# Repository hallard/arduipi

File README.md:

ArduiPi
=======

ArduiPi is a shield for Raspberry Pi that brings Arduino low level extented I/O to Raspberry Pi.

Detailed Description
====================

Everything is documented on this decicated [page][3]

**Schematic**  

**Board**  
![board] (https://raw.github.com/hallard/arduipi/master/ArduiPi-V1.1-brd.png)

Check out news and other projects on my [blog][4] 

[3]: http://hallard.me/arduipi-the-shield-that-brings-arduino-to-raspberry-pi/
[4]: http://hallard.me

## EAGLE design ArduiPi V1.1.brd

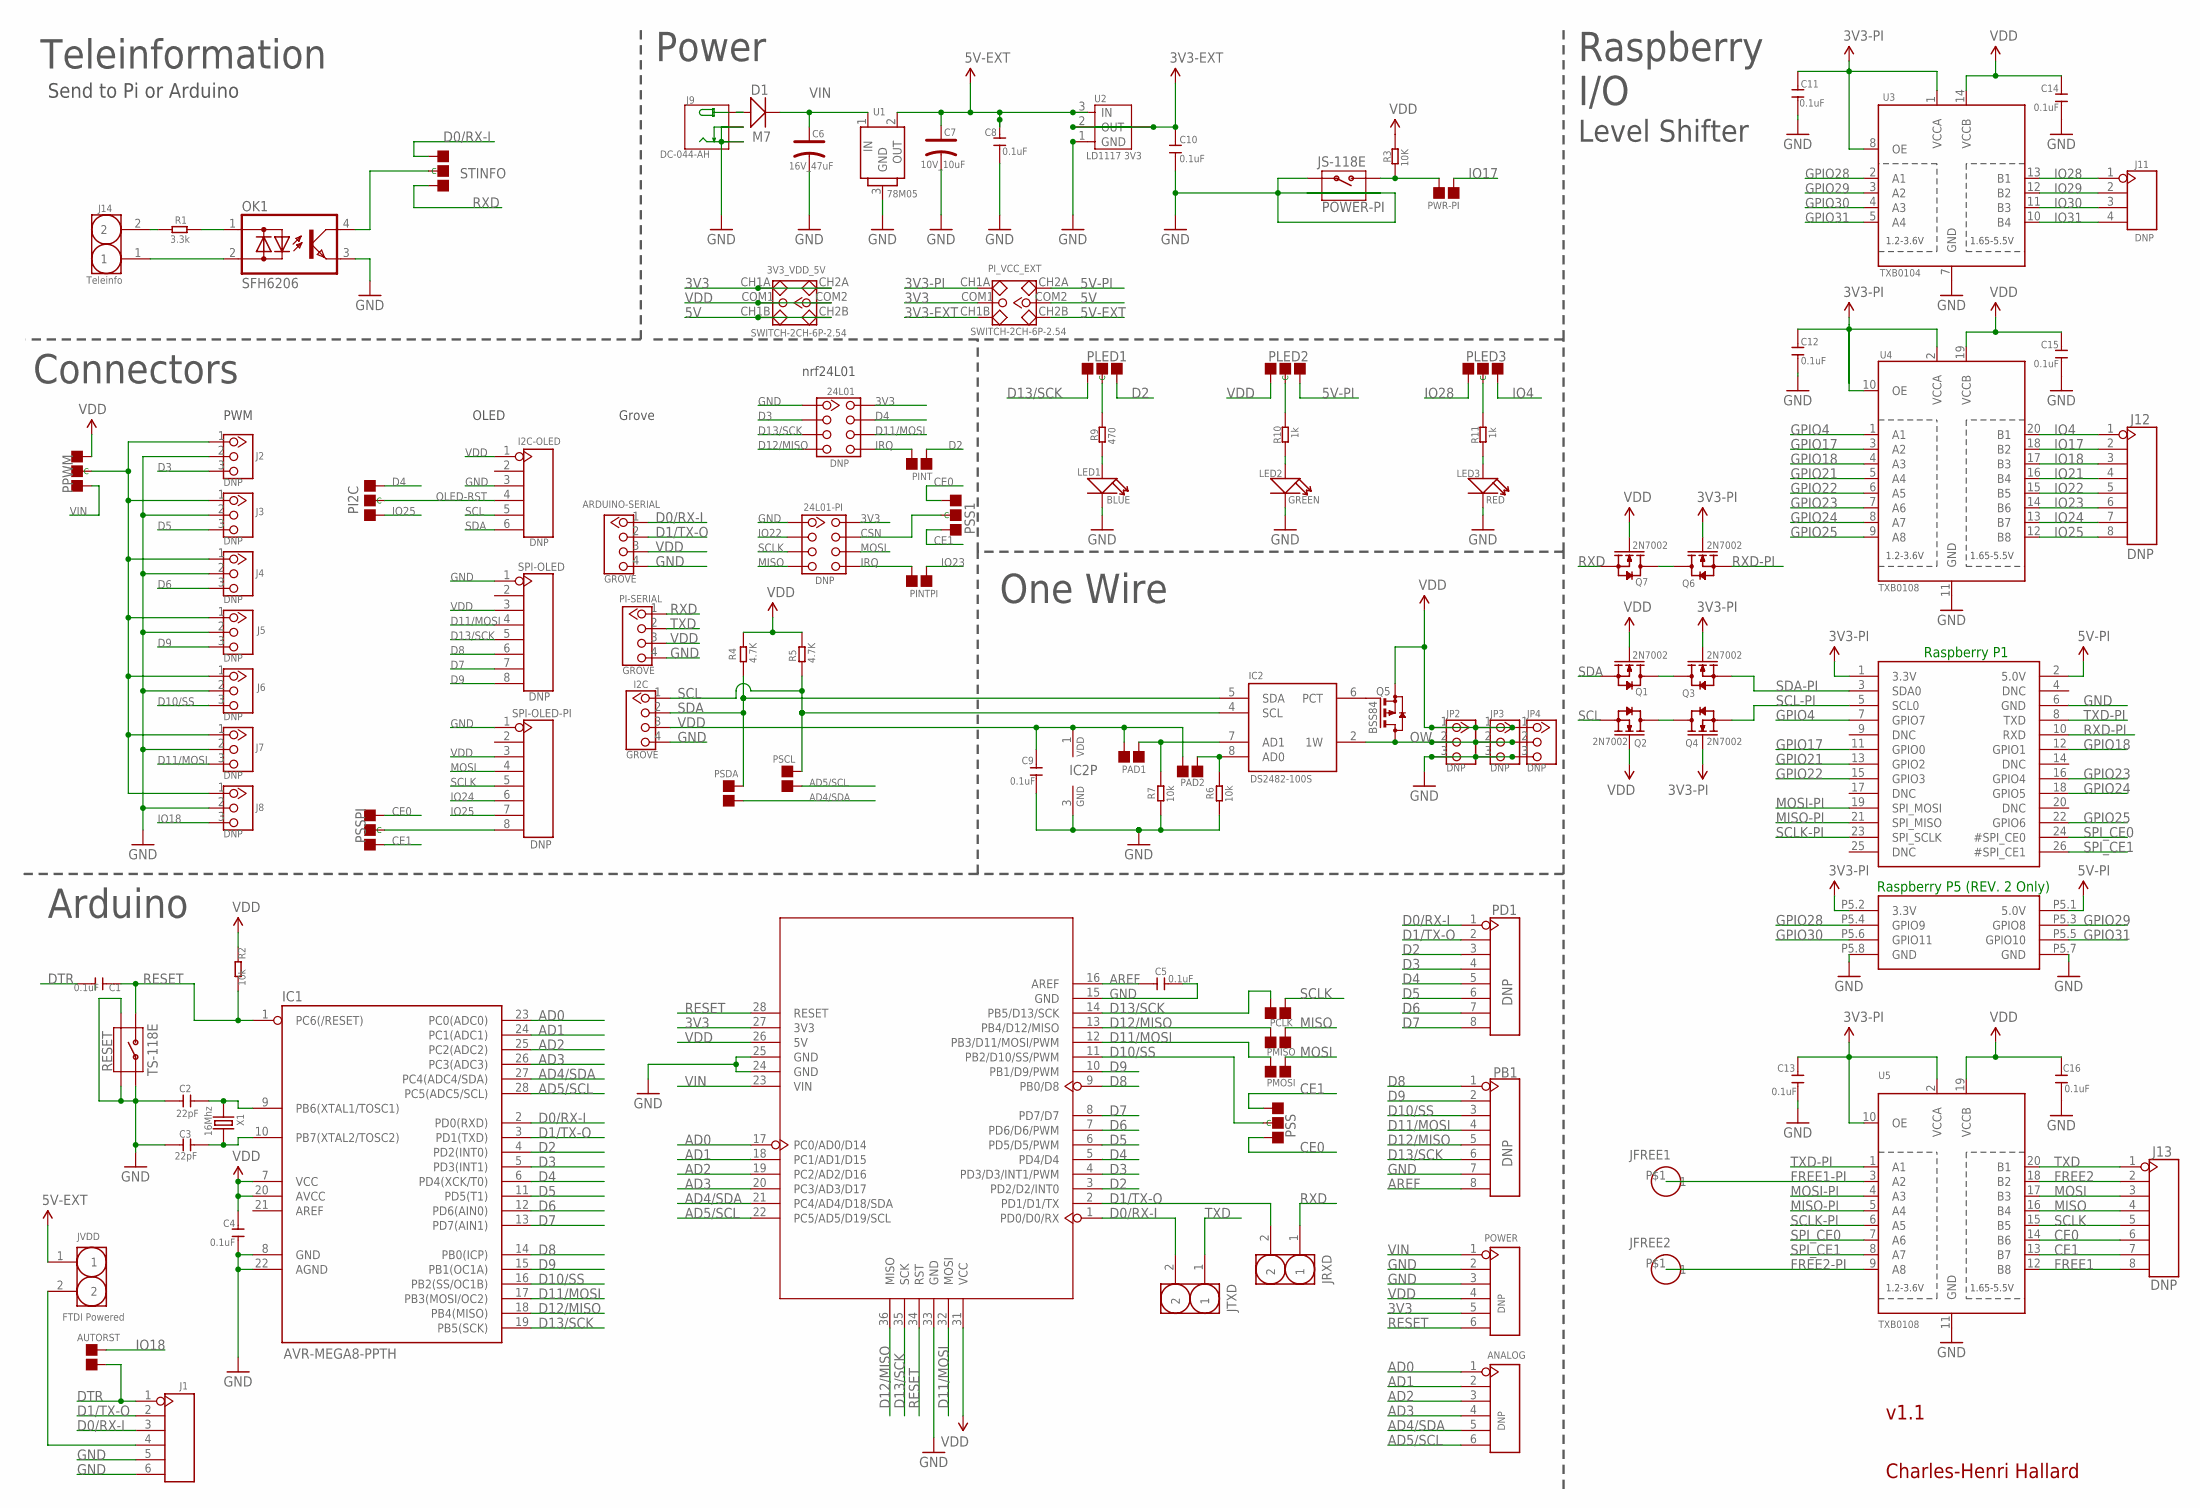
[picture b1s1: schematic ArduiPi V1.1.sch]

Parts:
3V3_VDD_5V: SWITCH-2CH-6P-2.54; 6P-2CH-2.54-7.6X3.0
24L01, 24L01-PI: DNP; 2X4P-2.54
ANALOG: DNP; 6P-2.54-65/35MIL
ARDUINO-SERIAL: GROVE; 4P-LEADED-2.0
AUTORST: PSDA; 2P-SMD-1.78X1.27
C1, C4, C5, C8, C9, C10, C11, C12, C13, C14, C15, C16: 0.1uF; C0603
C2, C3: 22pF; C0603
C6: 16V_47uF; AVX-C
C7: 10V_10uF; AVX-A
D1: M7; D2010
I2C: GROVE; 4P-LEADED-2.0
I2C-OLED: DNP; 6P-2.54-65/35MIL
IC1: AVR-MEGA8-PPTH; DIL28-3
IC2: DS2482-100S; SO08
J1: HEADER-6P-65/35MIL; 6P-2.54-65/35MIL
J2, J3, J4, J5, J6, J7, J8: DNP; 3P-2.54
J9: DC-044-AH; DC-044
J11: DNP; 4P-65/35MIL
J12, J13: DNP; 8P-2.54-65/35MIL
J14: Teleinfo; 2P-2.54
JFREE1, JFREE2: HEADER-1P-32; 1P-60/32MIL
JP2, JP3, JP4: DNP; 3P-2.54
JRXD: J2; 2P-2.54
JTXD: J1; 2P-2.54
JVDD: FTDI Powered; 2P-2.54
LED1: BLUE; LED-0603
LED2: GREEN; LED-0603
LED3: RED; LED-0603
OK1: SFH6206; DIL4-SMD
PAD1: PAD1; 2P-SMD-1.78X1.27; PARTNO DNP
PAD2: PAD2; 2P-SMD-1.78X1.27; PARTNO DNP
PB1: DNP; 8P-2.54-65/35MIL
PCLK: PCLK; 2P-SMD-1.78X1.27
PD1: DNP; 8P-2.54-65/35MIL
PI2C: PAD-JUMPER-3P-40*40; 3P-SMD-4.1X1.5; PARTNO DNP
PI-P1: PI-P1; RASPBERRYPI_SHIELD
PI-SERIAL: GROVE; 4P-LEADED-2.0
PINT: PINT; 2P-SMD-1.78X1.27
PINTPI: PINTPI; 2P-SMD-1.78X1.27
PI_VCC_EXT: SWITCH-2CH-6P-2.54; 6P-2CH-2.54-7.6X3.0
PLED1, PLED3: PAD-JUMPER-3P-40*40; 3P-SMD-4.1X1.5; PARTNO DNP
PLED2: PAD-JUMPER-3P-40*40; 3P-SMD-4.1X1.5
PMISO: PMISO; 2P-SMD-1.78X1.27
PMOSI: PMOSI; 2P-SMD-1.78X1.27
POWER: DNP; 6P-2.54-65/35MIL
POWER-PI: JS-118E; 4P-SMD-7X3.5X3.5H
PPWM: PAD-JUMPER-3P-40*40; 3P-SMD-4.1X1.5; PARTNO DNP
PSCL: PSCL; 2P-SMD-1.78X1.27
PSDA: PSDA; 2P-SMD-1.78X1.27
PSS: PAD-JUMPER-3P-40*40; 3P-SMD-4.1X1.5
PSS1: PAD-JUMPER-3P-40*40; 3P-SMD-4.1X1.5; PARTNO DNP
PSSPI: PAD-JUMPER-3P-40*40; 3P-SMD-4.1X1.5; PARTNO DNP
PWR-PI: PINT; 2P-SMD-1.78X1.27
Q1, Q2, Q3, Q4, Q6, Q7: 2N7002; SOT23
Q5: BSS84; SOT23
R1: 3.3k; R0603
R2, R6, R7: 10k; R0603
R3: 10K; R0603
R4, R5: 4.7K; R0603
R9: 470; R0603
R10, R11: 1k; R0603
RESET: TS-118E; 4P-SMD-7X3.5X3.5H
SPI-OLED: DNP; 8P-2.54-65/35MIL
SPI-OLED-PI: DNP; 8P-2.54-65/35MIL
STINFO: PAD-JUMPER-3P-40*40; 3P-SMD-4.1X1.5
U1: 78M05; TO252
U2: LD1117 3V3; SOT-223
U3: TXB0104; TSSOP14
U4, U5: TXB0108; TSSOP20
U6: ARDUINO'W/-SILK; ARDUINO
X1: 16Mhz; 2P-SMD-5X3.2

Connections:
3V3: 3V3_VDD_5V.CH1A, 3V3_VDD_5V.CH2A, 24L01.8, 24L01-PI.8, PI_VCC_EXT.COM1, POWER.5, U6.27 (3V3)
3V3-EXT: C10.2, PI_VCC_EXT.CH1B, U2.2 (OUT), U2.TER (TAB)
3V3-PI: C11.1, C12.1, C13.1, PI-P1.1 (3.3V), PI-P1.P5.2 (3.3V), PI_VCC_EXT.CH1A, Q3.1 (G), Q4.1 (G), Q6.1 (G), U3.1 (VCCA), U3.8 (OE), U4.2 (VCCA), U4.10 (OE), U5.2 (VCCA), U5.10 (OE)
5V: 3V3_VDD_5V.CH1B, 3V3_VDD_5V.CH2B, PI_VCC_EXT.COM2
5V-EXT: C7.+, C8.2, JVDD.1, PI_VCC_EXT.CH2B, U1.2 (OUT), U2.3 (IN)
5V-PI: PI-P1.2 (5.0V), PI-P1.P5.1 (5.0V), PI_VCC_EXT.CH2A, PLED2.11 (R)
AD0: ANALOG.1, IC1.23 (PC0(ADC0)), U6.17 (PC0/AD0/D14)
AD1: ANALOG.2, IC1.24 (PC1(ADC1)), U6.18 (PC1/AD1/D15)
AD2: ANALOG.3, IC1.25 (PC2(ADC2)), U6.19 (PC2/AD2/D16)
AD3: ANALOG.4, IC1.26 (PC3(ADC3)), U6.20 (PC3/AD3/D17)
AD4/SDA: ANALOG.5, IC1.27 (PC4(ADC4/SDA)), PSDA.1, U6.21 (PC4/AD4/D18/SDA)
AD5/SCL: ANALOG.6, IC1.28 (PC5(ADC5/SCL)), PSCL.1, U6.22 (PC5/AD5/D19/SCL)
AREF: C5.1, PB1.8, U6.16 (AREF)
CE0: J13.6, PSS.11 (R), PSS1.00 (L), PSSPI.11 (R), U5.14 (B6)
CE1: J13.7, PSS.00 (L), PSS1.11 (R), PSSPI.00 (L), U5.13 (B7)
CSN: 24L01-PI.7, PSS1.MM (C)
D0/RX-I: ARDUINO-SERIAL.1, IC1.2 (PD0(RXD)), J1.3, JTXD.2, PD1.1, STINFO.00 (L), U6.1 (PD0/D0/RX)
D1/TX-O: ARDUINO-SERIAL.2, IC1.3 (PD1(TXD)), J1.2, JRXD.2, PD1.2, U6.2 (PD1/D1/TX)
D2: IC1.4 (PD2(INT0)), PD1.3, PINT.1, PLED1.11 (R), U6.3 (PD2/D2/INT0)
D3: 24L01.2, IC1.5 (PD3(INT1)), J2.3, PD1.4, U6.4 (PD3/D3/INT1/PWM)
D4: 24L01.7, IC1.6 (PD4(XCK/T0)), PD1.5, PI2C.11 (R), U6.5 (PD4/D4)
D5: IC1.11 (PD5(T1)), J3.3, PD1.6, U6.6 (PD5/D5/PWM)
D6: IC1.12 (PD6(AIN0)), J4.3, PD1.7, U6.7 (PD6/D6/PWM)
D7: IC1.13 (PD7(AIN1)), PD1.8, SPI-OLED.7, U6.8 (PD7/D7)
D8: IC1.14 (PB0(ICP)), PB1.1, SPI-OLED.6, U6.9 (PB0/D8)
D9: IC1.15 (PB1(OC1A)), J5.3, PB1.2, SPI-OLED.8, U6.10 (PB1/D9/PWM)
D10/SS: IC1.16 (PB2(SS/OC1B)), J6.3, PB1.3, PSS.MM (C), U6.11 (PB2/D10/SS/PWM)
D11/MOSI: 24L01.6, IC1.17 (PB3(MOSI/OC2)), J7.3, PB1.4, PMOSI.2, SPI-OLED.4, U6.12 (PB3/D11/MOSI/PWM), U6.32 (MOSI)
D12/MISO: 24L01.4, IC1.18 (PB4(MISO)), PB1.5, PMISO.2, U6.13 (PB4/D12/MISO), U6.36 (MISO)
D13/SCK: 24L01.3, IC1.19 (PB5(SCK)), PB1.6, PCLK.2, PLED1.00 (L), SPI-OLED.5, U6.14 (PB5/D13/SCK), U6.35 (SCK)
DTR: AUTORST.1, C1.2, J1.1
FREE1: J13.8, U5.12 (B8)
FREE1-PI: JFREE1.P$1, U5.3 (A2)
FREE2: J13.2, U5.18 (B2)
FREE2-PI: JFREE2.P$1, U5.9 (A8)
GND: 24L01.1, 24L01-PI.1, ARDUINO-SERIAL.4, C2.2, C3.2, C4.1, C5.2, C6.-, C7.-, C8.1, C9.2, C10.1, C11.2, C12.2, C13.2, C14.2, C15.2, C16.2, I2C.4, I2C-OLED.3, IC1.8 (GND), IC1.22 (AGND), IC2.3 (GND), J1.5, J1.6, J2.2, J3.2, J4.2, J5.2, J6.2, J7.2, J8.2, J9.-, J9.CDN, JP2.3, JP3.3, JP4.3, LED1.-, LED2.-, LED3.-, OK1.3 (E), PB1.7, PI-P1.6 (GND), PI-P1.P5.7 (GND), PI-P1.P5.8 (GND), PI-SERIAL.4, POWER.2, POWER.3, POWER-PI.1, POWER-PI.S1, POWER-PI.S2, R6.1, R7.1, RESET.1, RESET.S1, RESET.S2, SPI-OLED.1, SPI-OLED-PI.1, U1.3 (GND), U2.1 (GND), U3.7 (GND), U4.11 (GND), U5.11 (GND), U6.15 (GND), U6.24 (GND), U6.25 (GND), U6.33 (GND)
GPIO4: PI-P1.7 (GPIO7), U4.1 (A1)
GPIO17: PI-P1.11 (GPIO0), U4.3 (A2)
GPIO18: PI-P1.12 (GPIO1), U4.4 (A3)
GPIO21: PI-P1.13 (GPIO2), U4.5 (A4)
GPIO22: PI-P1.15 (GPIO3), U4.6 (A5)
GPIO23: PI-P1.16 (GPIO4), U4.7 (A6)
GPIO24: PI-P1.18 (GPIO5), U4.8 (A7)
GPIO25: PI-P1.22 (GPIO6), U4.9 (A8)
GPIO28: PI-P1.P5.4 (GPIO9), U3.2 (A1)
GPIO29: PI-P1.P5.3 (GPIO8), U3.3 (A2)
GPIO30: PI-P1.P5.6 (GPIO11), U3.4 (A3)
GPIO31: PI-P1.P5.5 (GPIO10), U3.5 (A4)
IO4: J12.1, PLED3.11 (R), U4.20 (B1)
IO17: J12.2, PWR-PI.1, U4.18 (B2)
IO18: AUTORST.2, J8.3, J12.3, U4.17 (B3)
IO21: J12.4, U4.16 (B4)
IO22: 24L01-PI.2, J12.5, U4.15 (B5)
IO23: J12.6, PINTPI.1, U4.14 (B6)
IO24: J12.7, SPI-OLED-PI.6, U4.13 (B7)
IO25: J12.8, PI2C.00 (L), SPI-OLED-PI.7, U4.12 (B8)
IO28: J11.1, PLED3.00 (L), U3.13 (B1)
IO29: J11.2, U3.12 (B2)
IO30: J11.3, U3.11 (B3)
IO31: J11.4, U3.10 (B4)
IRQ: 24L01.5, 24L01-PI.5, PINT.2, PINTPI.2
MISO: 24L01-PI.4, J13.4, PMISO.1, U5.16 (B4)
MISO-PI: PI-P1.21 (SPI_MISO), U5.5 (A4)
MOSI: 24L01-PI.6, J13.3, PMOSI.1, SPI-OLED-PI.4, U5.17 (B3)
MOSI-PI: PI-P1.19 (SPI_MOSI), U5.4 (A3)
unnamed: OK1.4 (C), STINFO.MM (C)
unnamed: IC2.8 (AD0), PAD2.1, R6.2
unnamed: C3.1, IC1.10 (PB7(XTAL2/TOSC2)), X1.1
unnamed: C2.1, IC1.9 (PB6(XTAL1/TOSC1)), X1.2
unnamed: Q1.3 (D), Q3.3 (D)
unnamed: Q2.3 (D), Q4.3 (D)
unnamed: Q6.3 (D), Q7.3 (D)
unnamed: OK1.1 (AC1), R1.1
unnamed: J14.1, OK1.2 (AC2)
unnamed: J1.4, JVDD.2
unnamed: IC2.7 (AD1), PAD1.1, R7.2
unnamed: D1.+, J9.+
unnamed: LED3.+, R11.2
unnamed: J14.2, R1.2
unnamed: IC2.6 (PCT), Q5.1 (G)
unnamed: PLED1.MM (C), R9.1
unnamed: LED1.+, R9.2
unnamed: LED2.+, R10.2
unnamed: PLED3.MM (C), R11.1
unnamed: PLED2.MM (C), R10.1
unnamed: J2.1, J3.1, J4.1, J5.1, J6.1, J7.1, J8.1, PPWM.MM (C)
unnamed: POWER-PI.2, PWR-PI.2, R3.2
OLED-RST: I2C-OLED.4, PI2C.MM (C)
OW: IC2.2 (1W), JP2.2, JP3.2, JP4.2, Q5.3 (D)
RESET: C1.1, IC1.1 (PC6(/RESET)), POWER.6, R2.2, RESET.2, U6.28 (RESET), U6.34 (RST)
RXD: JRXD.1, PI-SERIAL.1, Q7.2 (S), STINFO.11 (R)
RXD-PI: PI-P1.10 (RXD), Q6.2 (S)
SCL: I2C.1, I2C-OLED.5, IC2.4 (SCL), PSCL.2, Q2.2 (S), R5.1
SCL-PI: PI-P1.5 (SCL0), Q4.2 (S)
SCLK: 24L01-PI.3, J13.5, PCLK.1, SPI-OLED-PI.5, U5.15 (B5)
SCLK-PI: PI-P1.23 (SPI_SCLK), U5.6 (A5)
SDA: I2C.2, I2C-OLED.6, IC2.5 (SDA), PSDA.2, Q1.2 (S), R4.1
SDA-PI: PI-P1.3 (SDA0), Q3.2 (S)
SPI_CE0: PI-P1.24 (#SPI_CE0), U5.7 (A6)
SPI_CE1: PI-P1.26 (#SPI_CE1), U5.8 (A7)
SSPI: PSSPI.MM (C), SPI-OLED-PI.8
TXD: J13.1, JTXD.1, PI-SERIAL.2, U5.20 (B1)
TXD-PI: PI-P1.8 (TXD), U5.1 (A1)
VDD: 3V3_VDD_5V.COM1, 3V3_VDD_5V.COM2, ARDUINO-SERIAL.3, C4.2, C9.1, C14.1, C15.1, C16.1, I2C.3, I2C-OLED.1, IC1.7 (VCC), IC1.20 (AVCC), IC2.1 (VDD), JP2.1, JP3.1, JP4.1, PAD1.2, PAD2.2, PI-SERIAL.3, PLED2.00 (L), POWER.4, PPWM.00 (L), Q1.1 (G), Q2.1 (G), Q5.2 (S), Q7.1 (G), R2.1, R3.1, R4.2, R5.2, SPI-OLED.3, SPI-OLED-PI.3, U3.14 (VCCB), U4.19 (VCCB), U5.19 (VCCB), U6.26 (5V), U6.31 (VCC)
VIN: C6.+, D1.-, POWER.1, PPWM.11 (R), U1.1 (IN), U6.23 (VIN)

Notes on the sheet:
Teleinformation
Power
Charles-Henri Hallard
Raspberry I/O
Level Shifter
Send to Pi or Arduino
One Wire
Connectors
Arduino
Raspberry P1
Raspberry P5 (REV. 2 Only)
PWM
OLED
Grove
nrf24L01
v1.1

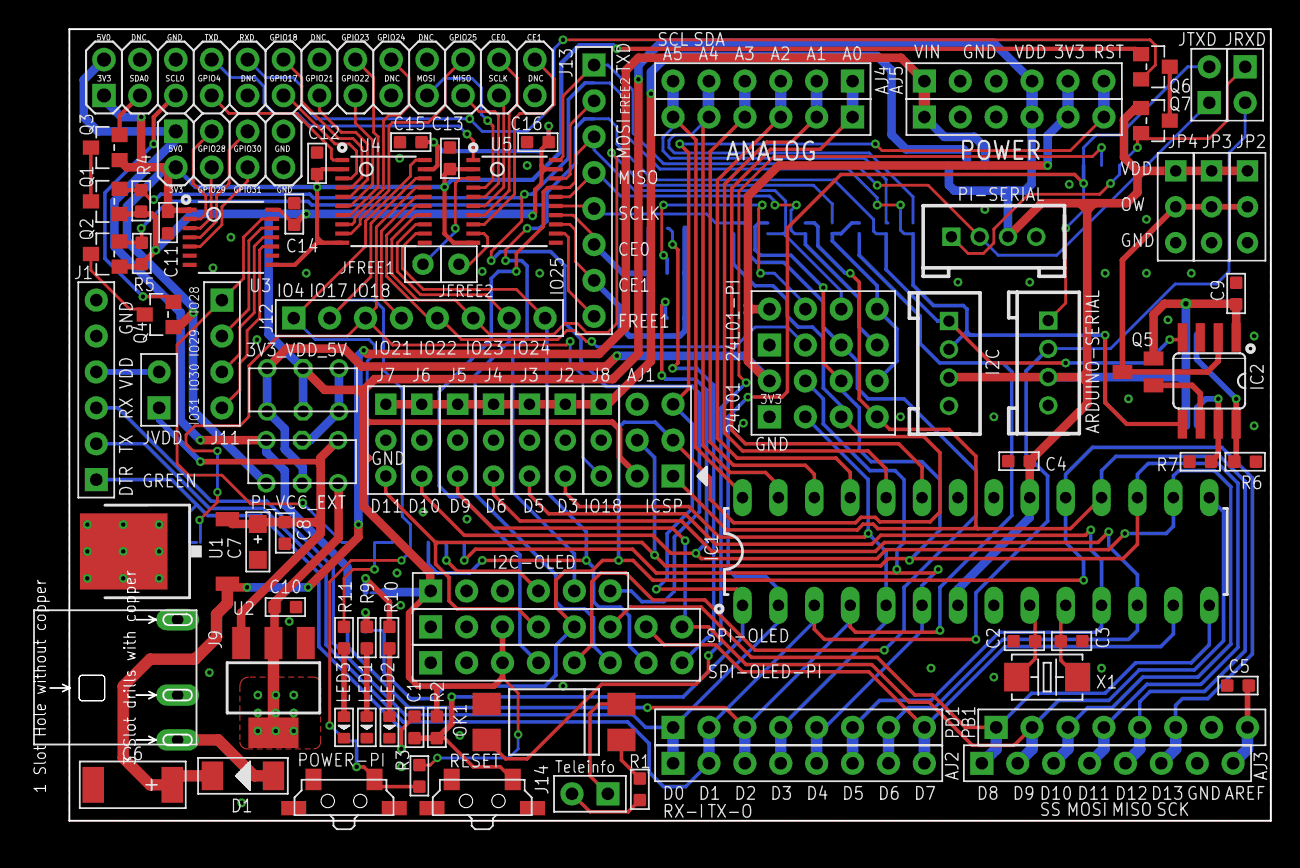
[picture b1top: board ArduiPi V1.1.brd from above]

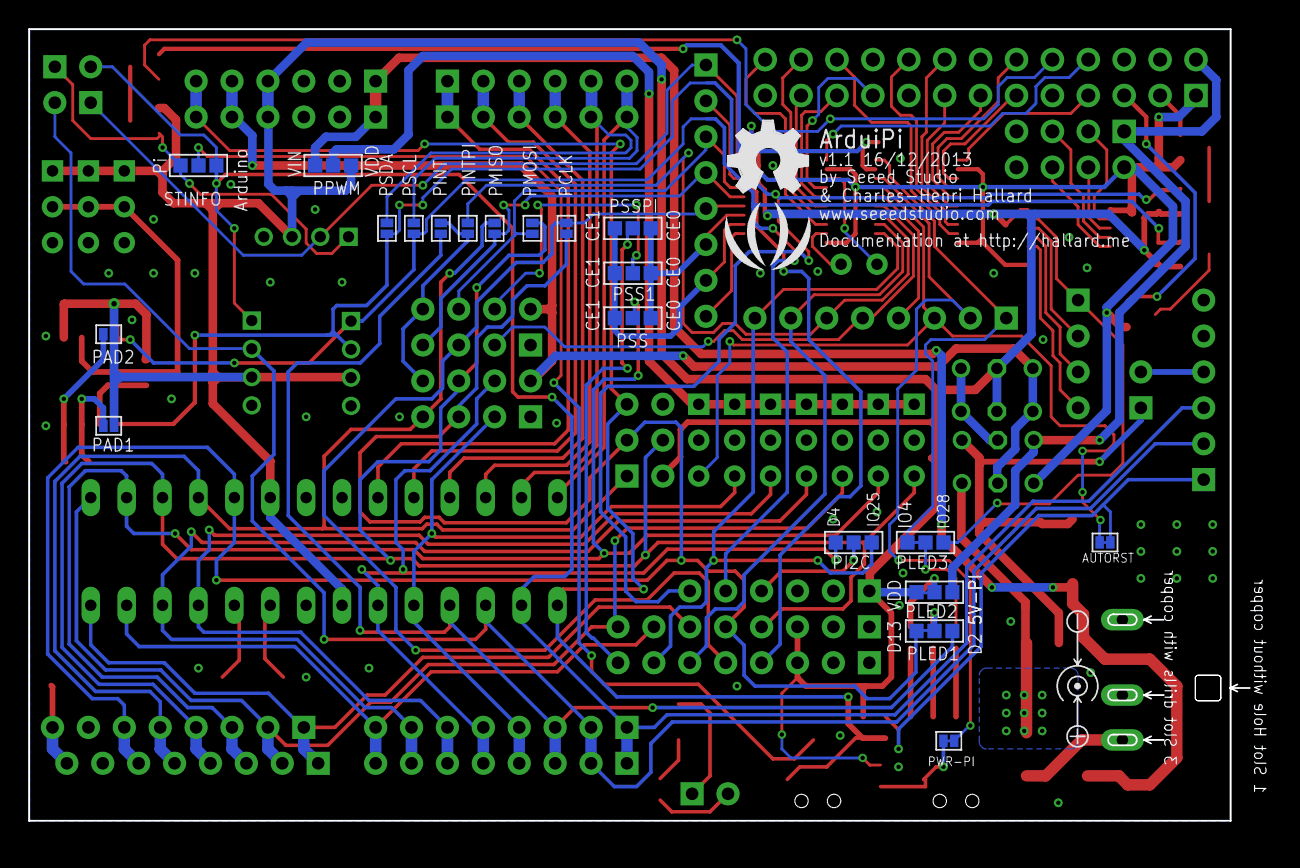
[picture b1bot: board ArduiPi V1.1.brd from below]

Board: 2 copper layers, 86.4 x 56.0 mm, 107 parts (22 on the bottom side), 105 nets.

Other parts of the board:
U$3: LOGO_SILK
U$6: OSHW_FILLX200_NOTEXT

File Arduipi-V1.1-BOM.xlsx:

| Qty | Part | Value | Package | Seeed Part number | Digikey Part Number | Description
 | 2 | U4, U5 | TXB0108 | TSSOP20 | 156001001 TXB0108PW | 296-21527-1-ND | 8-Bit Bi-Directional Level Shifter
 | 1 | U3 | TXB0104 | TSSOP14 | 156002001 TXB0104PWR | 296-21929-1-ND | 4-Bit Bi-Directional Level Shifter
 | 1 | OK1 | SFH6206 | DIL4-SMD |  | SFH6206-2T | Optocoupler, Phototransistor Output, AC Input
 | 6 | Q1, Q2, Q3, Q4, Q6, Q7 | 2N7002 | SOT23 | 044008001
 | 1 | Q5 | CJ2305 | SOT23 | 0440210P1
 | 1 | POWER PI | TS-1188E | 4P-SMD-7X3.5X3.5H | 3100060P1 |  | Switch to power down PI
 | 1 | RESET | TS-1188E | 4P-SMD-7X3.5X3.5H | 3100060P1 |  | Reset Switch, same than the one present on Seeeduino V3
 | 1 | IC2 | DS2482-100S | SO08 |  | DS2482S-100+-ND | I2C to 1-Wire Host Adapter/Line Driver
 | 2 | 3V3_VDD_5V | SWITCH-2CH-6P-2.54 | 6P-2CH-2.54-7.6X3.0 | 301002001 |  | Same than the two present on Seeeduino V3
 | 2 | PI_VCC_EXT | SWITCH-2CH-6P-2.54 | 6P-2CH-2.54-7.6X3.0 | 301002001 |  | Same than the two present on Seeeduino V3
 | 1 | U2 | CJT1117-3.3 | SOT-223 | 1310190P1
 | 1 | U1 | CJ78M05 | TO252 | 1300040P1
 | 3 | ARDUINO-SERIAL, I2C, PI-SERIAL | GOVE | 4P-LEADED-2.0 | 3470130P1 |  | Grove Connector, the same than on the Seeeduino V3
 | 1 | J9 | DC-044-AH | DC-404 | 3410010P1 |  | Power Connector, the same than on the Seeeduino V3
 | 12 | C1, C4, C5, C8, C9, C10, C11, C12, C13, C14, C15, C16 | 100nF | 0603 | 0100020P1 |  | Standard surface mount Ceramic Capacitor
 | 1 | IC1 | DIP IC Socket | 2X14P-2.54 Row Spacing 7.62mm | 349003001
 | 1 | insert in IC1 Socket | ATMEGA328P-PU | 28-DIP | 1030050P1 need burn bootloader
 | 2 | C2, C3 | 22pF | 0603 | 0100620P1 |  | Capacitor that goes with AVR crystal
 | 1 | X1 | 16Mhz | 2P-SMD-5X3.2 | 0500290P1 |  | Crystal For AVR
 | 1 | R1 | 1.2k | 0603 | 001095001 |  | Standard surface mount resistor
 | 2 | R6, R7 | 10k | 0603 | 0010170P1 |  | Standard surface mount resistor
 | 1 | R3 | 10k | 0603 | 0010170P1 |  | Standard surface mount resistor
 | 1 | R2 | 10k | 0603 | 0010170P1 |  | Standard surface mount resistor
 | 2 | R4, R5 | 4.7K | 0603 | 0010030P1 |  | Standard surface mount resistor
 | 1 | R9 | 470 | 0603 |  |  | Standard surface mount resistor
 | 2 | R10, R11 | 1K | 0603 |  |  | Standard surface mount resistor
 | 1 | LED1 | BLUE | 0603 | 0330060P1 |  | Standard surface mount BLUE LED
 | 1 | LED2 | GREEN | 0603 | 0330010P1 |  | Standard surface mount GREEN LED
 | 1 | LED3 | RED | 0603 | 0330020P1 |  | Standard surface mount RED LED
 | 1 | D1 | 1N4004 | D2010 | 030003001 |  | Standard diode
 | 1 | C7 | 10uF | CPOL-AVX-A-10UF-10V | 0130040P1 |  | Standard Electrolytic Capacitor
 | 1 | C6 | 47uF | CPOL-AVX-C-47UF-16V | 013015001 |  | Standard Electrolytic Capacitor
 | 1 | PB1 | 2.54-8p female | 8P-2.54 | 3460590P1 |  | Arduino headers, same than on Seeeduino V3
 | 1 | POWER | 2.54-6p female | 6P-2.54-65/35MIL | 346057001 |  | Arduino headers, same than on Seeeduino V3
 | 1 | PD1 | 2.54-8p female | 8P-2.54 | 3460590P1 |  | Arduino headers, same than on Seeeduino V3
 | 1 | ANALOG | 2.54-6p female | 6P-2.54-65/35MIL | 346057001 |  | Arduino headers, same than on Seeeduino V3
 | 1 | RASPBERRY P1 | 2.54-2x13p female |  | 2x13p long female header |  | 2x13 double row 26 pins Raspberry PI Connector
 | 1 | J1 (FTDI connector) | 2.54-6p male | 6P-2.54 | 346075001 | HEADER-6P-2.54 | 6 pin FTDI Header
 | 1 | RASPBERRY P5 | DNP |  | 2x4p long female header |  | DNP
 | 1 | PPWM | DNP | 3P-SMD |  | Solder PAD
 | 1 | PSSPI | DNP | 3P-SMD |  | Solder PAD
 | 7 | J2, J3, J4, J5, J6, J7, J8 | DNP | 3P-2.54 |  | HEADER-3P-2.54
 | 2 | SPI-OLED, SPI-OLED-PI | DNP | 8P-2.54 |  | HEADER-8P-2.54
 | 1 | I2C-OLED | DNP | 6P-2.54 |  | HEADER-6P-2.54
 | 3 | PLED1, PLED2, PLED3 | DNP | 3P-SMD |  | Solder PAD
 | 2 | PAD1, PAD2 | DNP | 2P-SMD |  | Solder PAD
 | 2 | 24L01, 24L01-PI | DNP | 2X4P-2.54 |  | HEADER-2X4P-2.54
 | 2 | PINT, PINT-PI | DNP | 2P-SMD |  | Solder PAD
 | 1 | PSS1 | DNP | 3P-SMD |  | Solder PAD
 | 3 | JP2,JP3,JP4 | DNP | 3P-2.54 |  | HEADER-3P-2.54
 | 1 | PCLK | DNP | 2P-SMD |  | Solder PAD
 | 1 | PMISO | DNP | 2P-SMD |  | Solder PAD
 | 1 | PMOSI | DNP | 2P-SMD |  | Solder PAD
 | 1 | PSS | DNP | 3P-SMD |  | Solder PAD
 | 3 | JVDD, JRXD, JTXD | DNP | 2P-2.54 |  | HEADER-2P-2.54
 | 1 | J14 | DNP | 2P-2.54 |  | HEADER-2P-2.54
 | 1 | J11 | DNP | 4P-2.54 |  | HEADER-4P-2.54
 | 2 | J12, J13 | DNP | 8P-2.54 |  | HEADER-8P-2.54
 | 2 | JFREE1, JFREE2 | DNP | HOLE |  | HOLE
 | 1 | STINFO | DNP | 3P-SMD |  | Solder PAD
 | 1 | PWR-PI | DNP | 2P-SMD |  | Solder PAD
 | 1 | AUTORST | DNP | 2P-SMD |  | Solder PAD
 | 2 | PSDA, PSCL | DNP | 2P-SMD |  | Solder PAD

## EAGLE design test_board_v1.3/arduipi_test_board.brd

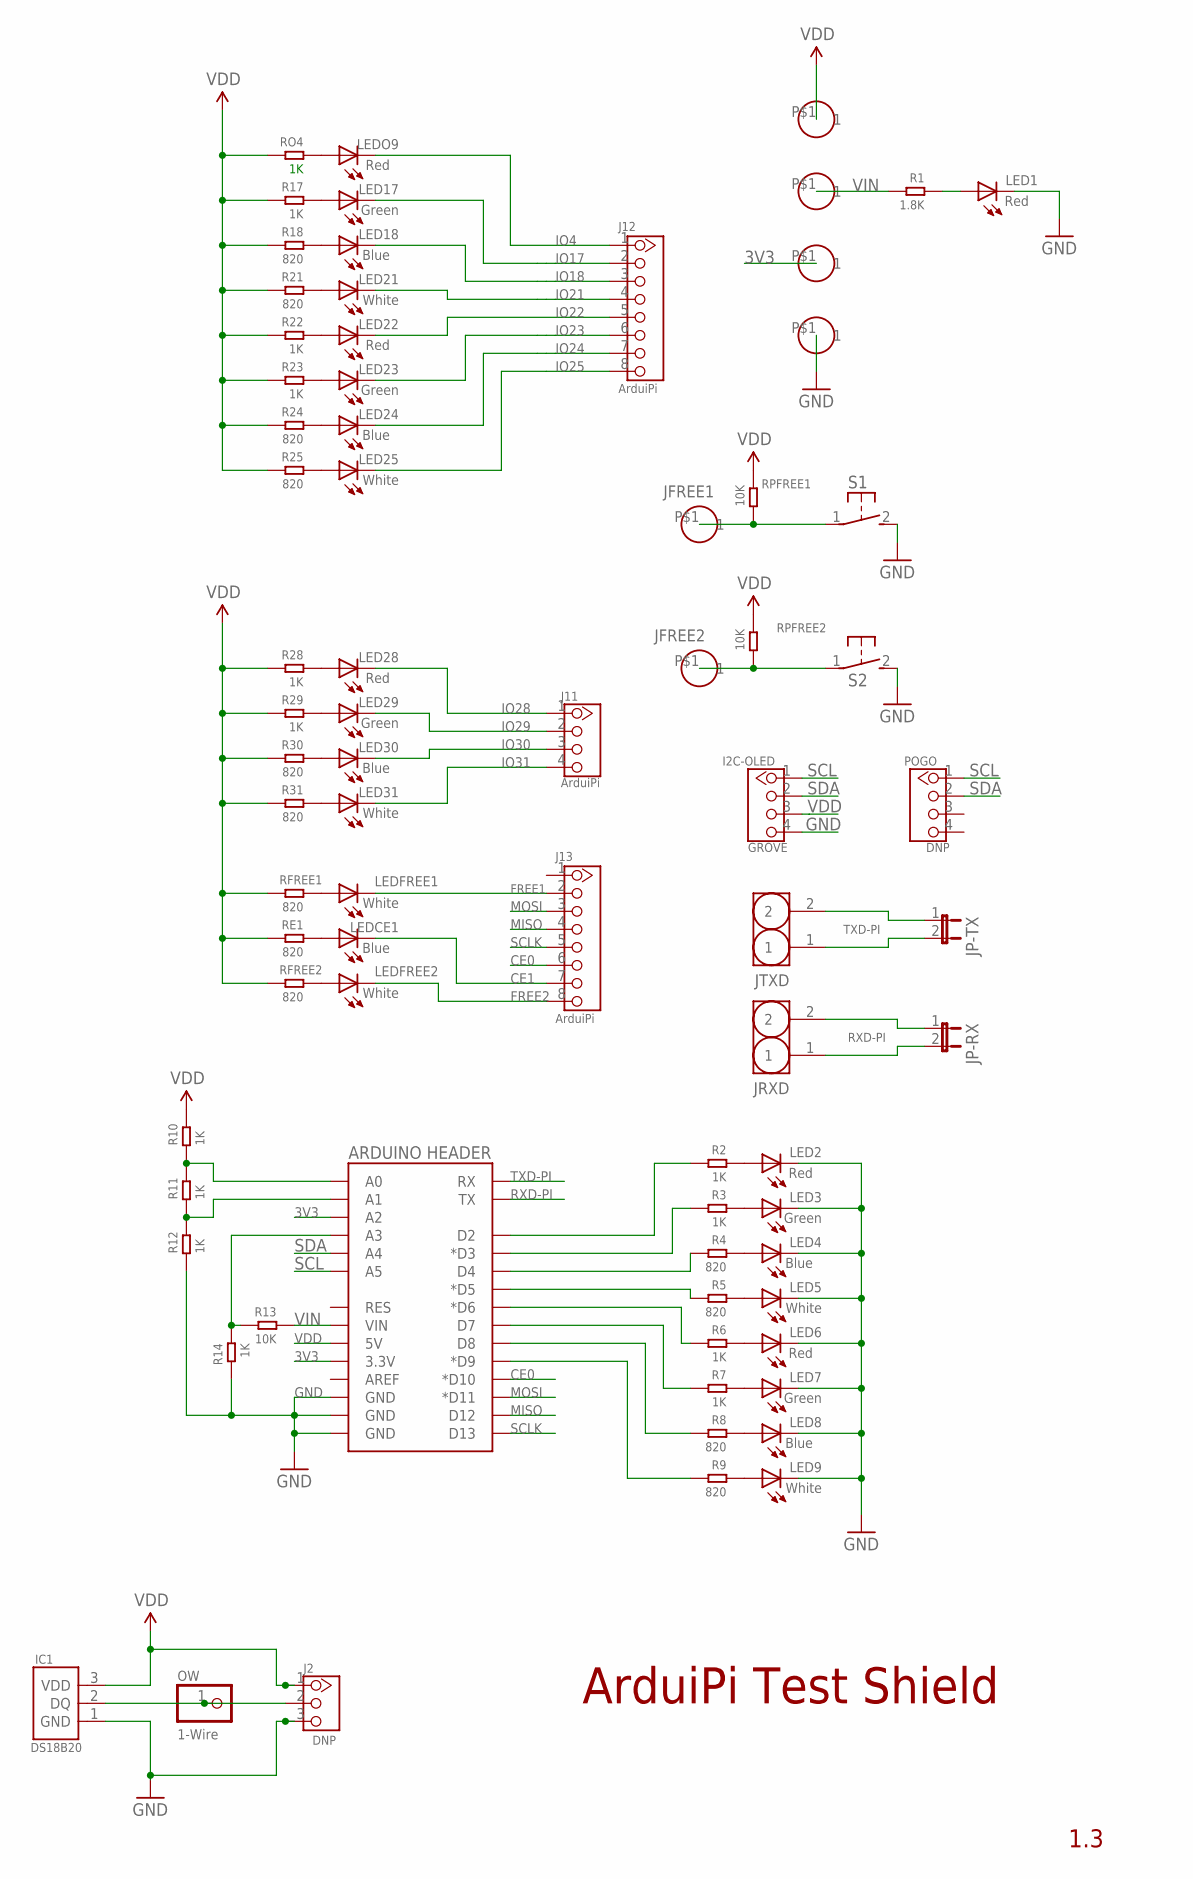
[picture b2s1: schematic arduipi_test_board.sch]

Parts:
3V3: HEADER-1P-32; 1P-60/32MIL
GND: HEADER-1P-32; 1P-60/32MIL
I2C-OLED: GROVE; 4P-LEADED-2.0
IC1: DS18B20; TO-92-TRIANGLE
J2: DNP; 3P-2.54
J11: ArduiPi; 4P-2.54-80/40MIL
J12, J13: ArduiPi; 8P-2.54-80/40MIL
JFREE1, JFREE2: HEADER-1P-32; 1P-60/32MIL
JP-RX: JUMPER-2PTH; 1X02
JP-TX: JUMPER-2PTH; 1X02
JRXD: J2; 2P-2.54
JTXD: J1; 2P-2.54
LED1, LED2, LED6, LED22, LED28: Red; LED3MM
LED3, LED7, LED17, LED23, LED29: Green; LED3MM
LED4, LED8, LED18, LED24, LED30: Blue; LED3MM
LED5, LED9, LED21, LED25, LED31: White; LED3MM
LEDCE1: Blue; LED3MM
LEDFREE1, LEDFREE2: White; LED3MM
LEDO9: Red; LED3MM
OW: 1-Wire; 1X01
POGO: DNP; 4P-LEADED-2.0
R1: 1.8K; 0204/7
R2, R3, R6, R7, R10, R11, R12, R14, R17, R22, R23, R28, R29: 1K; 0204/7
R4, R5, R8, R9, R18, R21, R24, R25, R30, R31: 820; 0204/7
R13: 10K; 0204/7
RE1: 820; 0204/7
RFREE1, RFREE2: 820; 0204/7
RO4: 1K; 0204/7
RPFREE1, RPFREE2: 10K; 0204/7
S1, S2: DTS-3
U1: ARDUINO HEADER; DUEMILANOVE_VIAS
VDD: HEADER-1P-32; 1P-60/32MIL
VIN: HEADER-1P-32; 1P-60/32MIL

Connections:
3V3: 3V3.P$1, U1.3.3V, U1.A2
CE0: J13.6, U1.D10 (*D10)
CE1: J13.7, LEDCE1.K (C)
DQ: IC1.2 (DQ), J2.2, OW.1
FREE1: J13.2, LEDFREE1.K (C)
FREE1-PI: JFREE1.P$1, RPFREE1.2, S1.1
FREE2: J13.8, LEDFREE2.K (C)
FREE2-PI: JFREE2.P$1, RPFREE2.1, S2.1
GND: GND.P$1, I2C-OLED.4, IC1.1 (GND), J2.3, LED1.K (C), LED2.K (C), LED3.K (C), LED4.K (C), LED5.K (C), LED6.K (C), LED7.K (C), LED8.K (C), LED9.K (C), R12.1, R14.2, S1.2, S2.2, U1.GND@0 (GND), U1.GND@1 (GND), U1.GND@2 (GND)
IO4: J12.1, LEDO9.K (C)
IO17: J12.2, LED17.K (C)
IO18: J12.3, LED18.K (C)
IO21: J12.4, LED21.K (C)
IO22: J12.5, LED22.K (C)
IO23: J12.6, LED23.K (C)
IO24: J12.7, LED24.K (C)
IO25: J12.8, LED25.K (C)
IO28: J11.1, LED28.K (C)
IO29: J11.2, LED29.K (C)
IO30: J11.3, LED30.K (C)
IO31: J11.4, LED31.K (C)
MISO: J13.4, U1.D12
MOSI: J13.3, U1.D11 (*D11)
unnamed: R11.1, R12.2, U1.A1
unnamed: R10.1, R11.2, U1.A0
unnamed: LED1.A, R1.1
unnamed: R13.2, R14.1, U1.A3
unnamed: LED2.A, R2.1
unnamed: JP-TX.2, JTXD.1
unnamed: LED3.A, R3.1
unnamed: LED4.A, R4.1
unnamed: LED5.A, R5.1
unnamed: JP-RX.2, JRXD.1
unnamed: LED6.A, R6.1
unnamed: LED7.A, R7.1
unnamed: LED8.A, R8.1
unnamed: LED9.A, R9.1
unnamed: LEDO9.A, RO4.1
unnamed: LED17.A, R17.1
unnamed: LED18.A, R18.1
unnamed: LED21.A, R21.1
unnamed: LED22.A, R22.1
unnamed: LED23.A, R23.1
unnamed: LED24.A, R24.1
unnamed: R9.2, U1.D9 (*D9)
unnamed: R8.2, U1.D8
unnamed: R7.2, U1.D7
unnamed: R6.2, U1.D6 (*D6)
unnamed: R5.2, U1.D5 (*D5)
unnamed: R4.2, U1.D4
unnamed: R3.2, U1.D3 (*D3)
unnamed: R2.2, U1.D2
unnamed: LED25.A, R25.1
unnamed: LEDFREE1.A, RFREE1.1
unnamed: LED28.A, R28.1
unnamed: LED29.A, R29.1
unnamed: LED30.A, R30.1
unnamed: LED31.A, R31.1
unnamed: LEDCE1.A, RE1.1
unnamed: LEDFREE2.A, RFREE2.1
RXD-PI: JP-RX.1, JRXD.2, U1.TX
SCL: I2C-OLED.1, POGO.1, U1.A5
SCLK: J13.5, U1.D13
SDA: I2C-OLED.2, POGO.2, U1.A4
TXD-PI: JP-TX.1, JTXD.2, U1.RX
VDD: I2C-OLED.3, IC1.3 (VDD), J2.1, R10.2, R17.2, R18.2, R21.2, R22.2, R23.2, R24.2, R25.2, R28.2, R29.2, R30.2, R31.2, RE1.2, RFREE1.2, RFREE2.2, RO4.2, RPFREE1.1, RPFREE2.2, U1.5V, VDD.P$1
VIN: R1.2, R13.1, U1.VIN, VIN.P$1

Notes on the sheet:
ArduiPi Test Shield
1.3

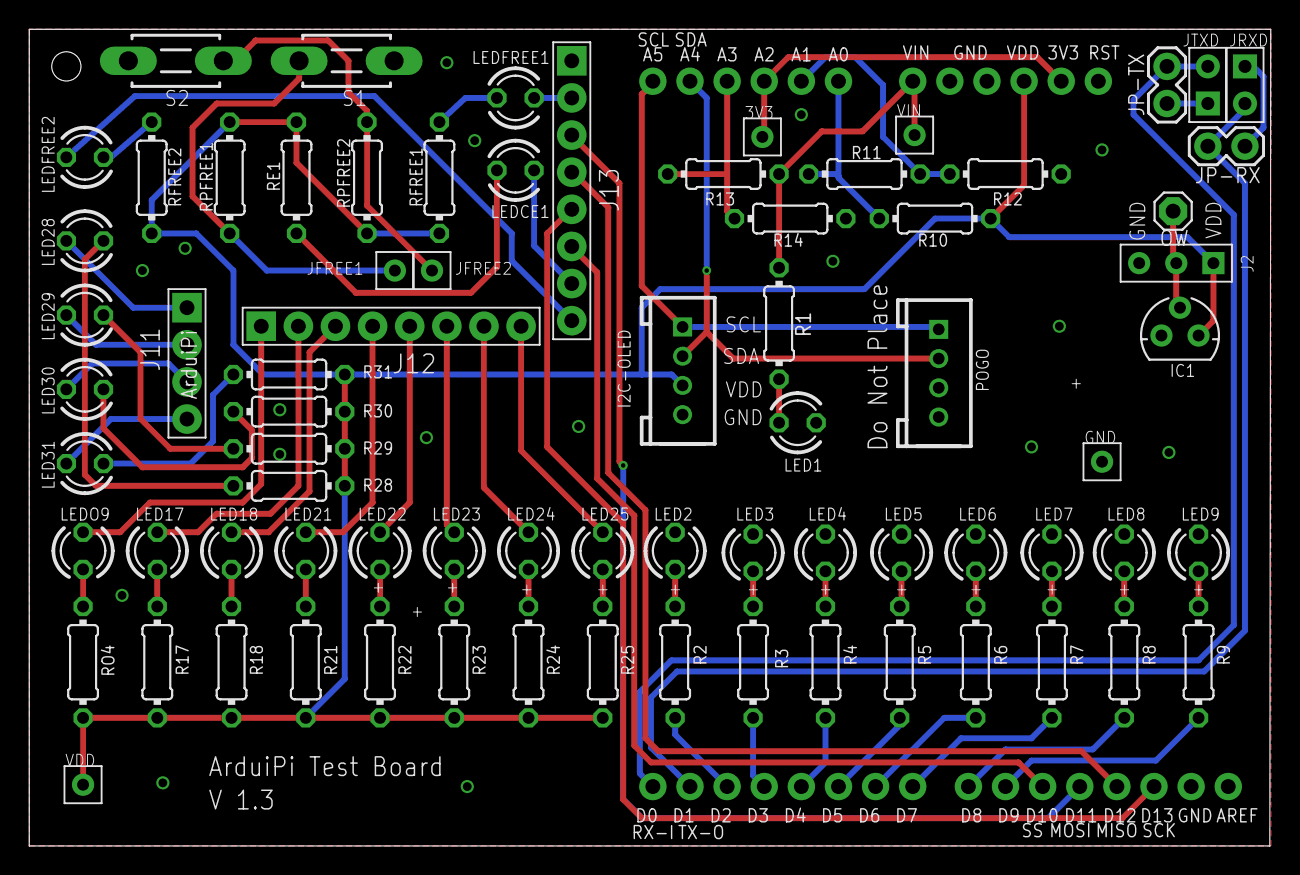
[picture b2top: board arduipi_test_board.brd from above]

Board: 2 copper layers, 85.0 x 55.9 mm, 76 parts (0 on the bottom side), 67 nets.

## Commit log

2012-10-02 Creation
    Added func descriptions
2012-10-02 Create gh-pages branch via GitHub
2012-10-04 Preliminary Schematic
2012-10-04 removed some files
2012-10-08 Added Seeedstudio link back
2012-10-08 ping back Seeedstudio blog
2012-10-09 Added link to wiki documentation
2012-11-06 Reordered Componnents on PCB for bettre view
2012-11-06 Final Design
    Final Design
2012-11-07 Added Pads
    Added pads for One Wire and Prototyping area
2013-02-28 Prototype Board
    ArduiPi First Prototype Board
2013-03-05 2nd Prototype Board
    2nd Version of the prototype board, near final version.
    Changes :
    - Removed R3 pullup from the output of the SFH6206
    - Changed Level Shifting of RX line, now goes through 2 new FET
    transistors Q7 and Q6 (BSS138 like I2C) and removed the connection of RX
    from the TXB0108 (U5)
2013-06-29 ArduiPi Production Version V0.9d
    ArduiPi Production Version V0.9d
2013-06-29 ArduiPi Test Board Shield
    ArduiPi Test Board Shield for testing ArduiPi board after production
2013-07-29 Creation
2013-07-30 Modification for SPI return test
2013-07-30 Bug Fixes
    Compilation problem
    put the serial to 9600 for test board
2013-07-30 Bug Fixes
    Set the serial to 9600 for test
    Flush the serial before test
    Grab the output of ArduiPi program to hex upcase
2013-08-08 Bug Fixe
    Set port D2..D9 to output in setup
    Removed I2C speed of 400KHz
2013-09-11 Set SPI speed to 1MHZ and limit I2C display
    Set SPI speed to 1MHZ
    Refresh I2C display only after received I2C test command to avoid I2C
    collision
2013-09-11 Set SPI Speed to 1MHZ, Avoid i2C collisions with OLED
    Set SPI Speed to 1MHZ
    Display enabled only when received 1st I2C command to avoid I2C
    collisions
2013-09-11 Updated to avoid I2C collision with OLED i2c
    change into IRQ, if we detect I2C detect issued from Pi we validate I2C
    test and start refresh OLED
2013-09-11 Set SPI speed to 1MHZ / removed i2C Ping
    Set SPI speed to 1MHZ
    removed i2c ping test
2013-09-11 bug fix on SPI set bus speed
    launching tool trying to set spi speed with --maxspeed 1000 was not
    working du to a bug on parsing option
2014-03-03 Creation
    Auto Reset file to enable firmware upload to Arduino from Arduino IDE
    using Raspberry PI Serial UART
2014-03-03 Creation
    Script to Reset Arduino without programming it
2014-03-03 Creation
    ArduiPi V1.0 Schematics
2014-03-22 Revision 1.1 of the board
2014-03-22 ArduiPi Arduino Bootloader
    ArduiPi bootloader
    Modified to have 2 flash led on D13 and blinking on uploading
2014-03-22 Revision 1.1 of the board BOM file
2014-03-22 Updated for V1.1 board
2014-03-22 Added Pictures

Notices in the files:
parts and their libraries:
SparkFun-Aesthetics: Licensing: CC v3.0 Share-Alike You are welcome to use this library for commercial purposes.
